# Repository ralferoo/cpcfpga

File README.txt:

PLEASE NOTE THAT THIS IS ONLY A PARTIAL REPOSITORY DUMP WHILE I TRY TO
SEPARATE PUBLIC AND PRIVATE PARTS...

-------------------------------------------------------------------------------

Contents
--------

This is the CPC FPGA project - a modern reimplementation of the Amstrad CPC
on an FPGA.

Whilst it's designed for use with the Amstrad CPC, the board could be
used for almost any 8-bit system. Alternatively, it could be used as a
cheap FPGA development board that includes a SCART socket, RAM, flash ROM,
PS/2 keyboard, twin joystick ports, tape input, etc...

The project is structured in these subdirectories:

bitstreams	Contains FPGA images that can be loaded from SD card
client		Contains Linux utilities to communicate with the board
datasheets	Miscellaneous datasheets (obtained publically, but are NOT
		part of this project)
docs		Various snippets of documentation I've written at various times
hardware/case	The case for revision 2 of CPC FPGA, for laser cutter use
hardware/eagle	The eagle schematic and circuit design for:
			homeboard30  (revision 1)
			homeboard99r (revision 2)
hardware/spice	Various spice analysis snippets
library/hdl	VHDL files that can be used in projects hosted on CPC FPGA
projects	Contains FPGA projects to be run on the CPC FPGA.
sidecar2	The firmware for the CPC FPGA suport chip
stuff		Old bits and bobs, to be deleted
Makefile	Used to build the system
README.txt	This file

-------------------------------------------------------------------------------

Building the CPC FPGA project
-----------------------------

The user part of CPC FPGA program can be built simply by running "make".

Other build targets:

all		Rebuild client and bitstreams
clean		Clean all build files, excluding final targets
bitstreams	Rebuild all the FPGA bitstream files

scan		Check to see if the CPC FPGA board is present
log		Keep an eye on the diagnostic log from the CPC FPGA board
dump		Dump the CPC FPGA image stored in the PROM
reload		Reload the CPC FPGA image stored in the PROM
xxx.load	Reload the CPC FPGA image for project xxx
xxx.program	Programs the CPC FPGA's PROM with the image for project xxx

sidecar2	Rebuild just the firmware
dfu		Install the firmware
reset		Resets the firmware

-------------------------------------------------------------------------------

LICENCES

The Atmega source code uses the LUFA library, licensed under the MIT library.
Please see licence/LUFA-License.txt for copyright information.

The schematic and board layout are currently licensed under the Creative
Commons Attribution-Share Alike 3.0.
Please see http://creativecommons.org/licenses/by-sa/3.0/ for more information.

If you make derivative works, you must license under a compatible licence
and include the following text:
Portions of this project are derived from CPC FPGA, (c) 2011-2013 Ranulf Doswell

Other than including the above attribution, you should rename the derivative
work so that it cannot be confused with the original CPC FPGA project, nor
can you refer to CPC FPGA in a manner that suggests the derivative work is
endorsed by CPC FGPA or used by CPC FPGA.

Any VHDL code is currently not open sourced unless explicitly mentioned.
The scope of the project is solely the hardware design and software for the
support chip.

If you need a commercial licence for the hardware portion of this project,
please contact licensing@ranulf.net for more information.

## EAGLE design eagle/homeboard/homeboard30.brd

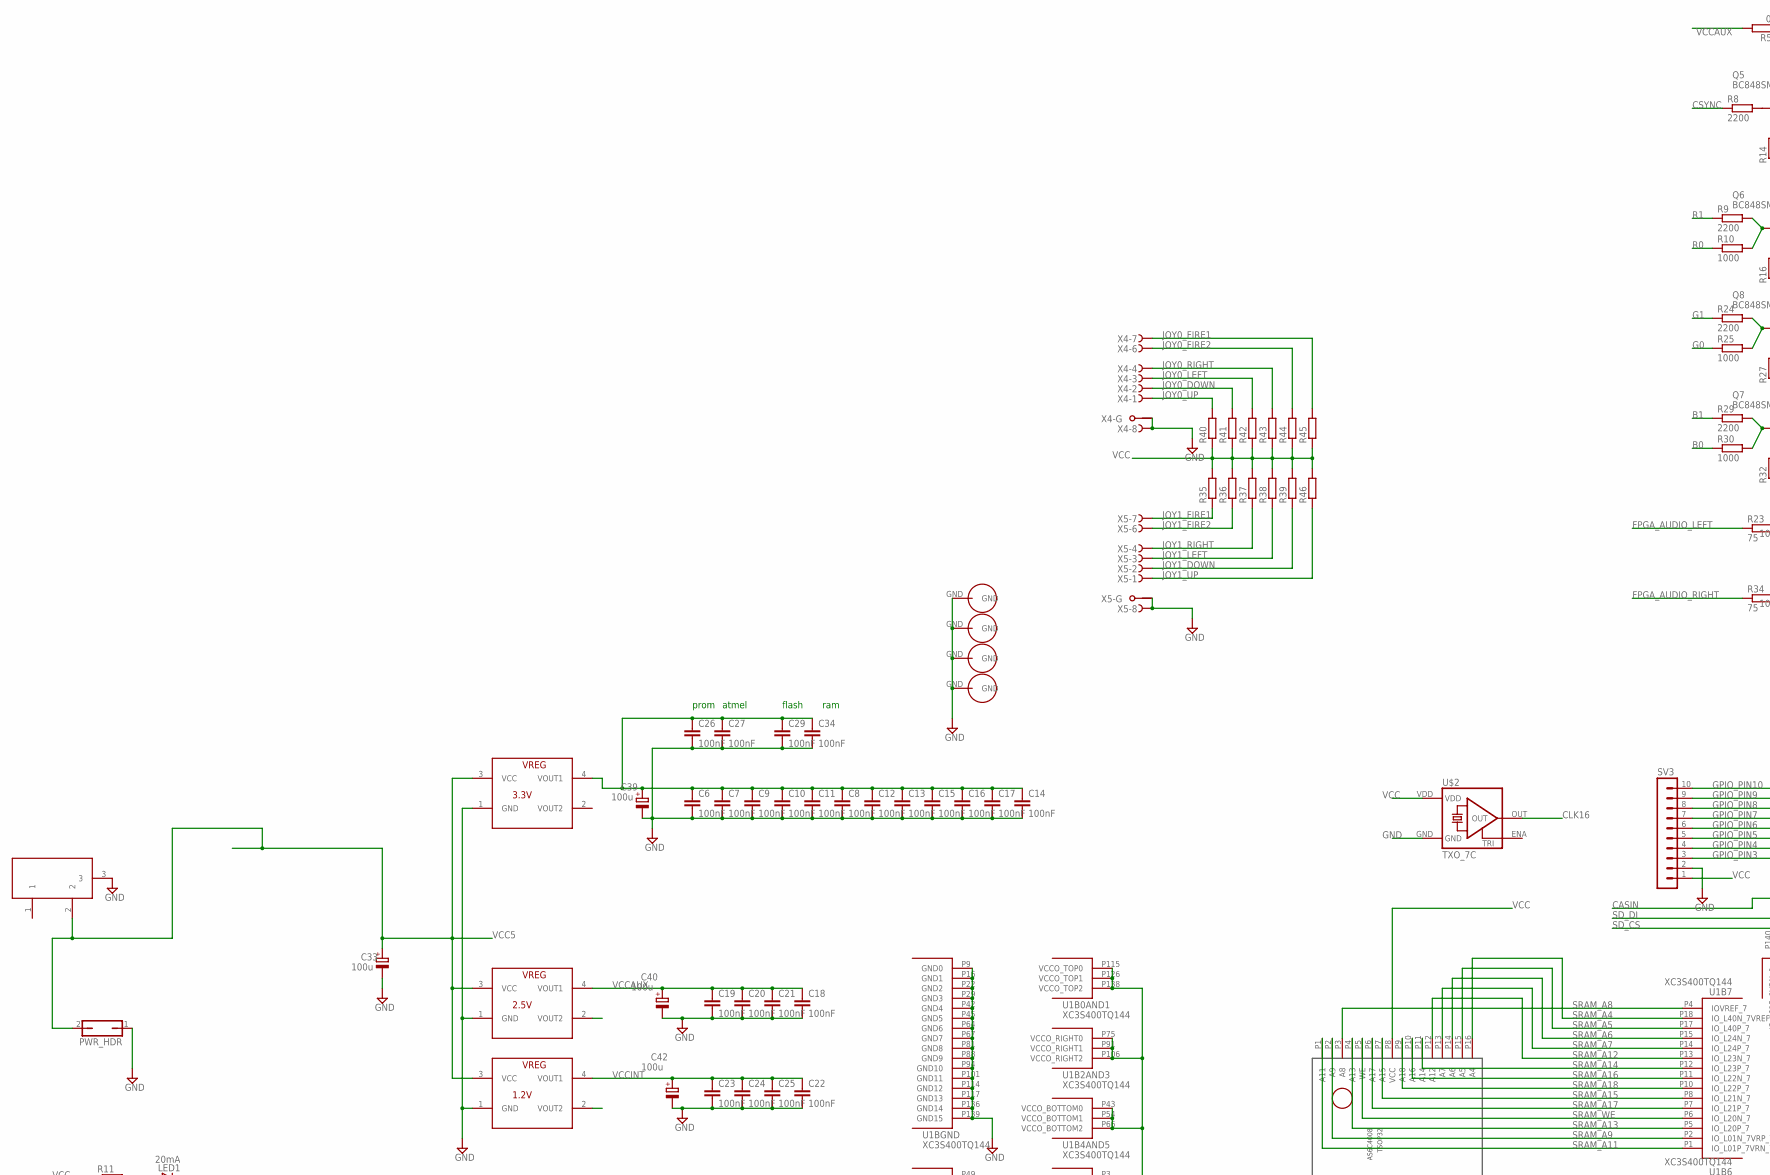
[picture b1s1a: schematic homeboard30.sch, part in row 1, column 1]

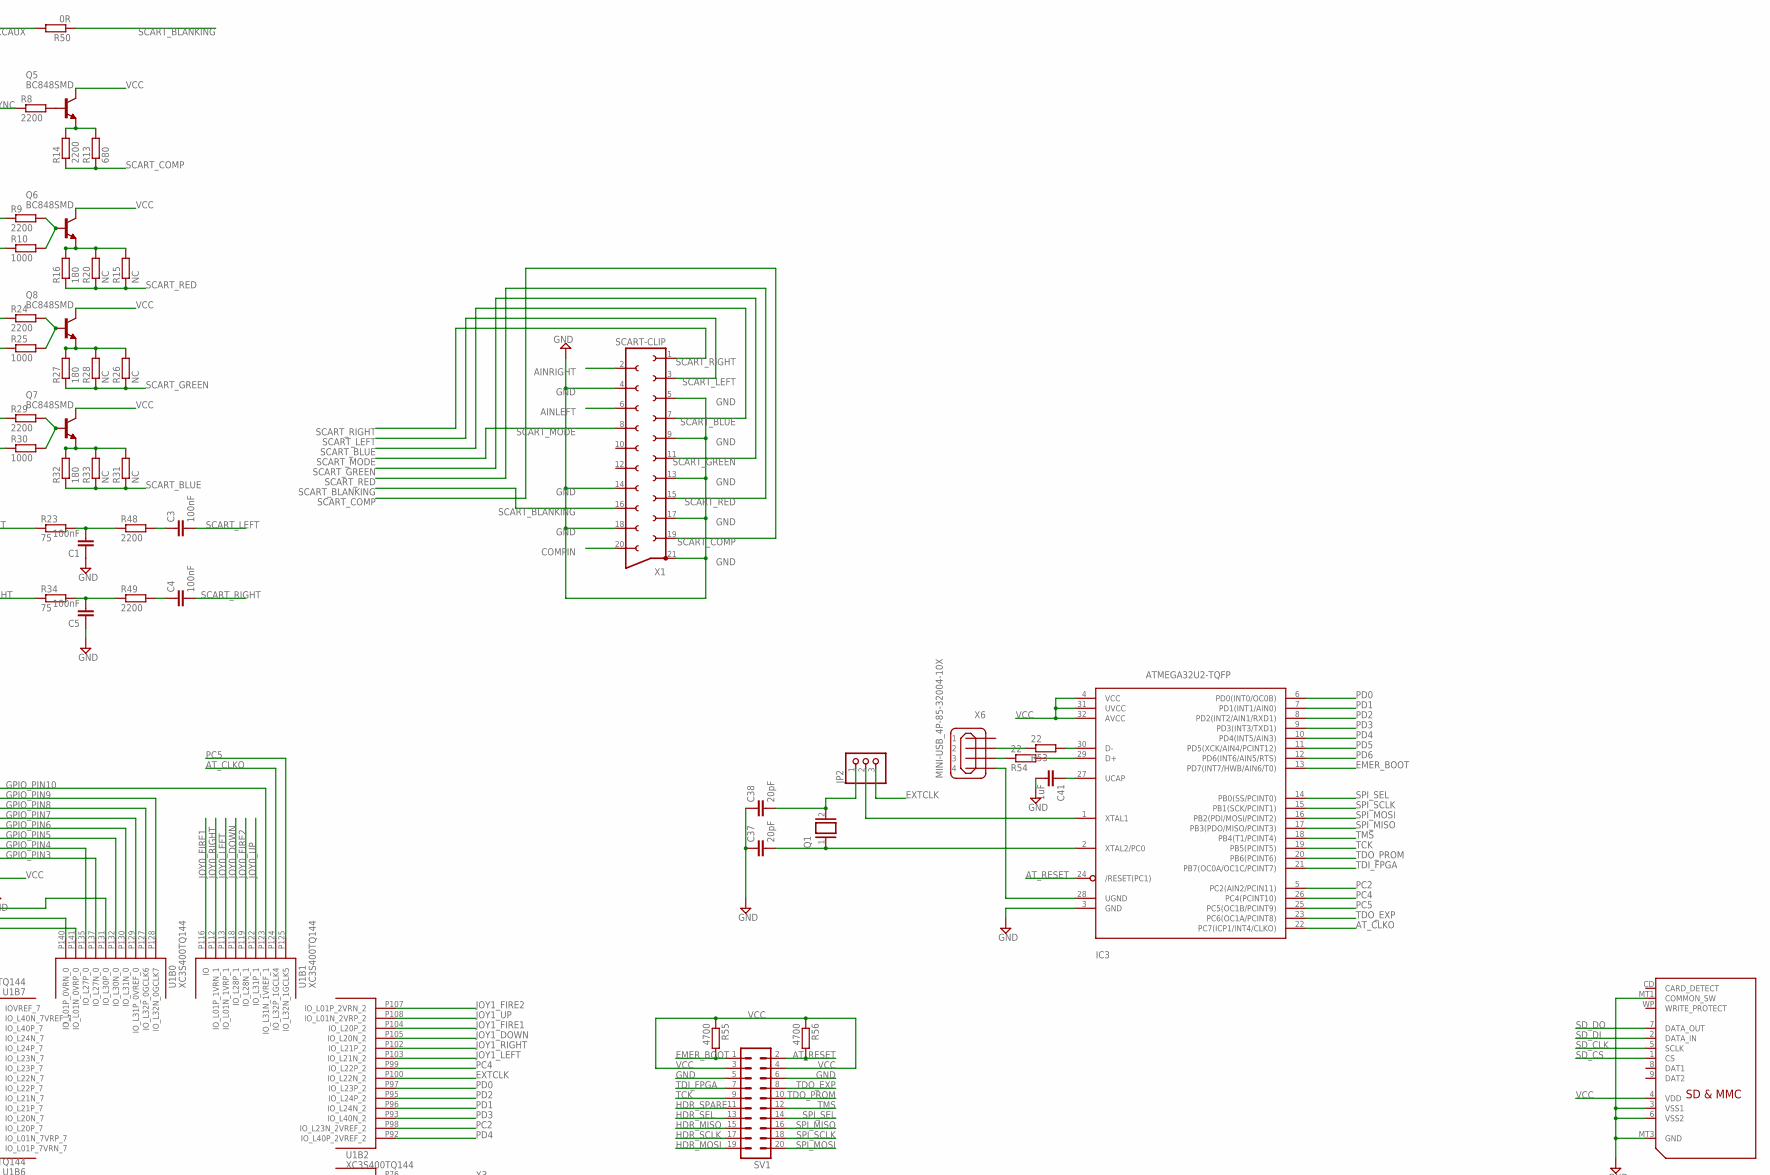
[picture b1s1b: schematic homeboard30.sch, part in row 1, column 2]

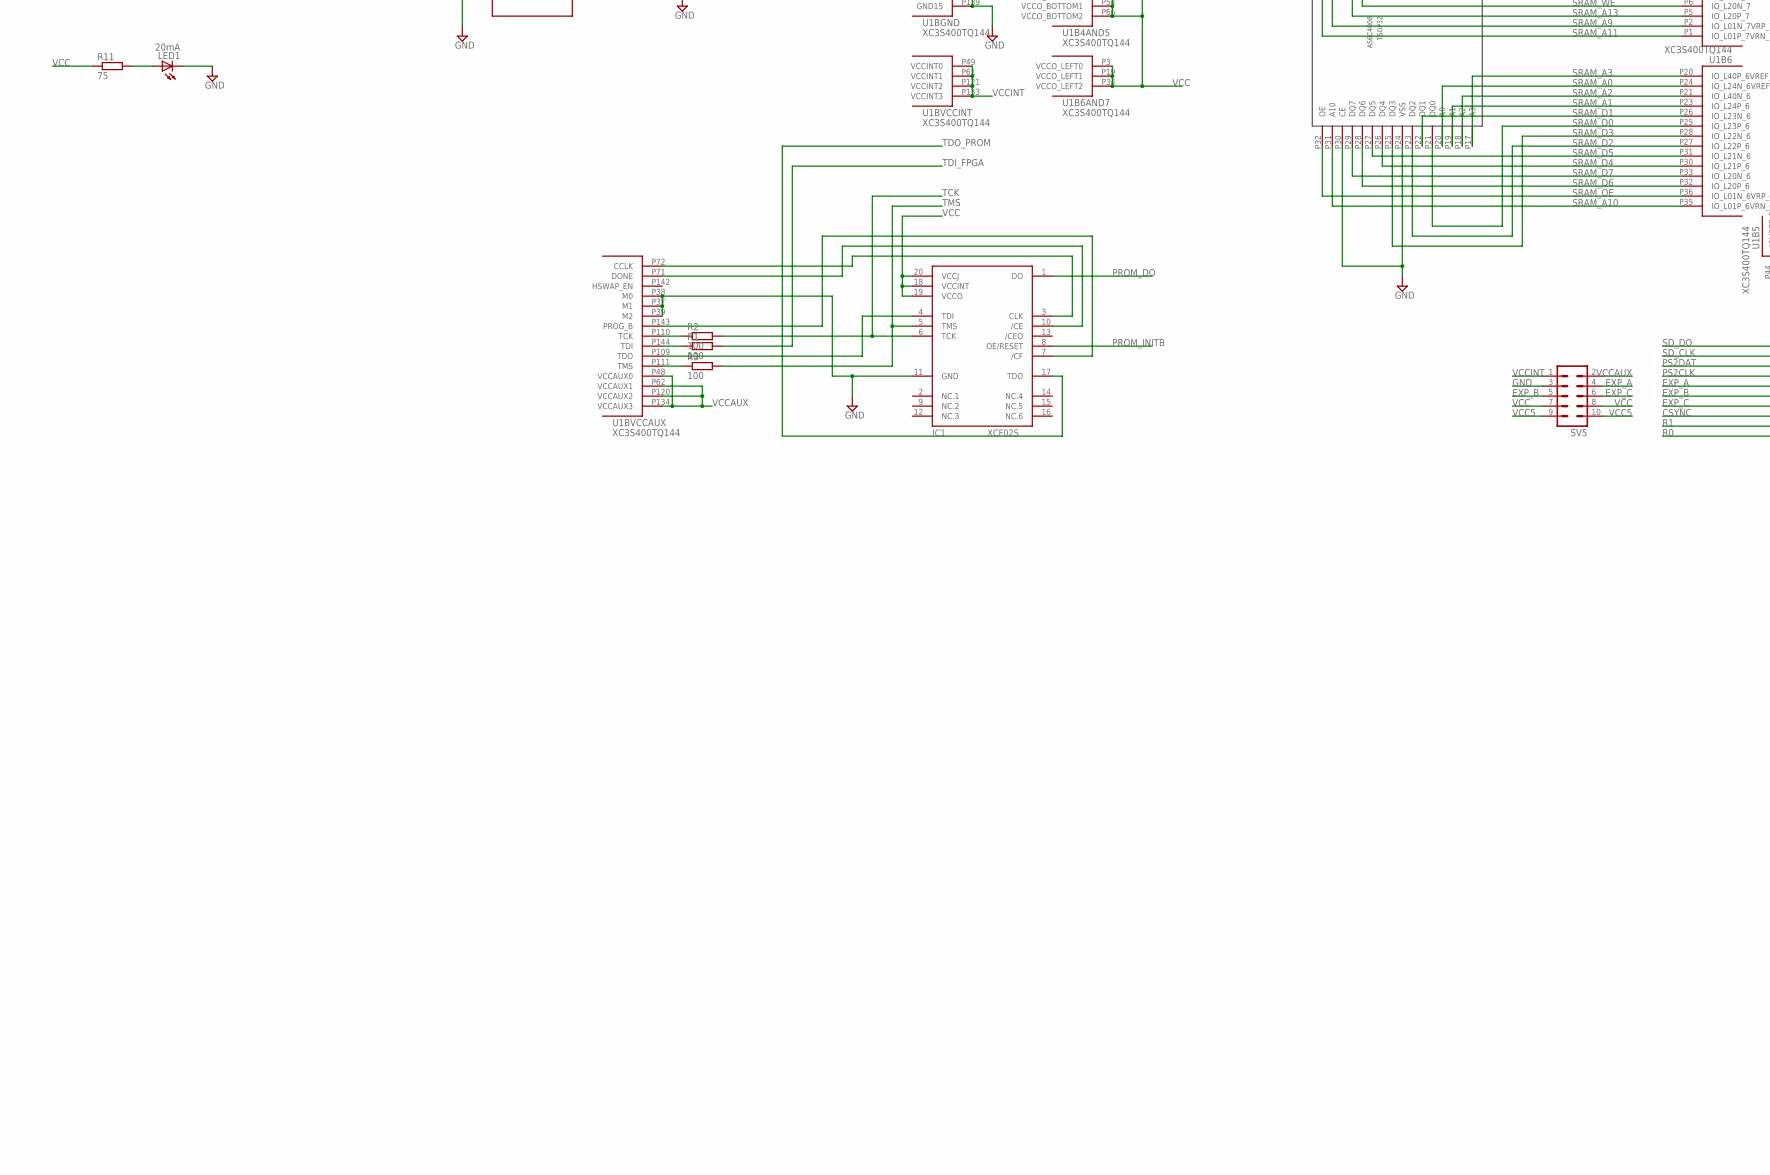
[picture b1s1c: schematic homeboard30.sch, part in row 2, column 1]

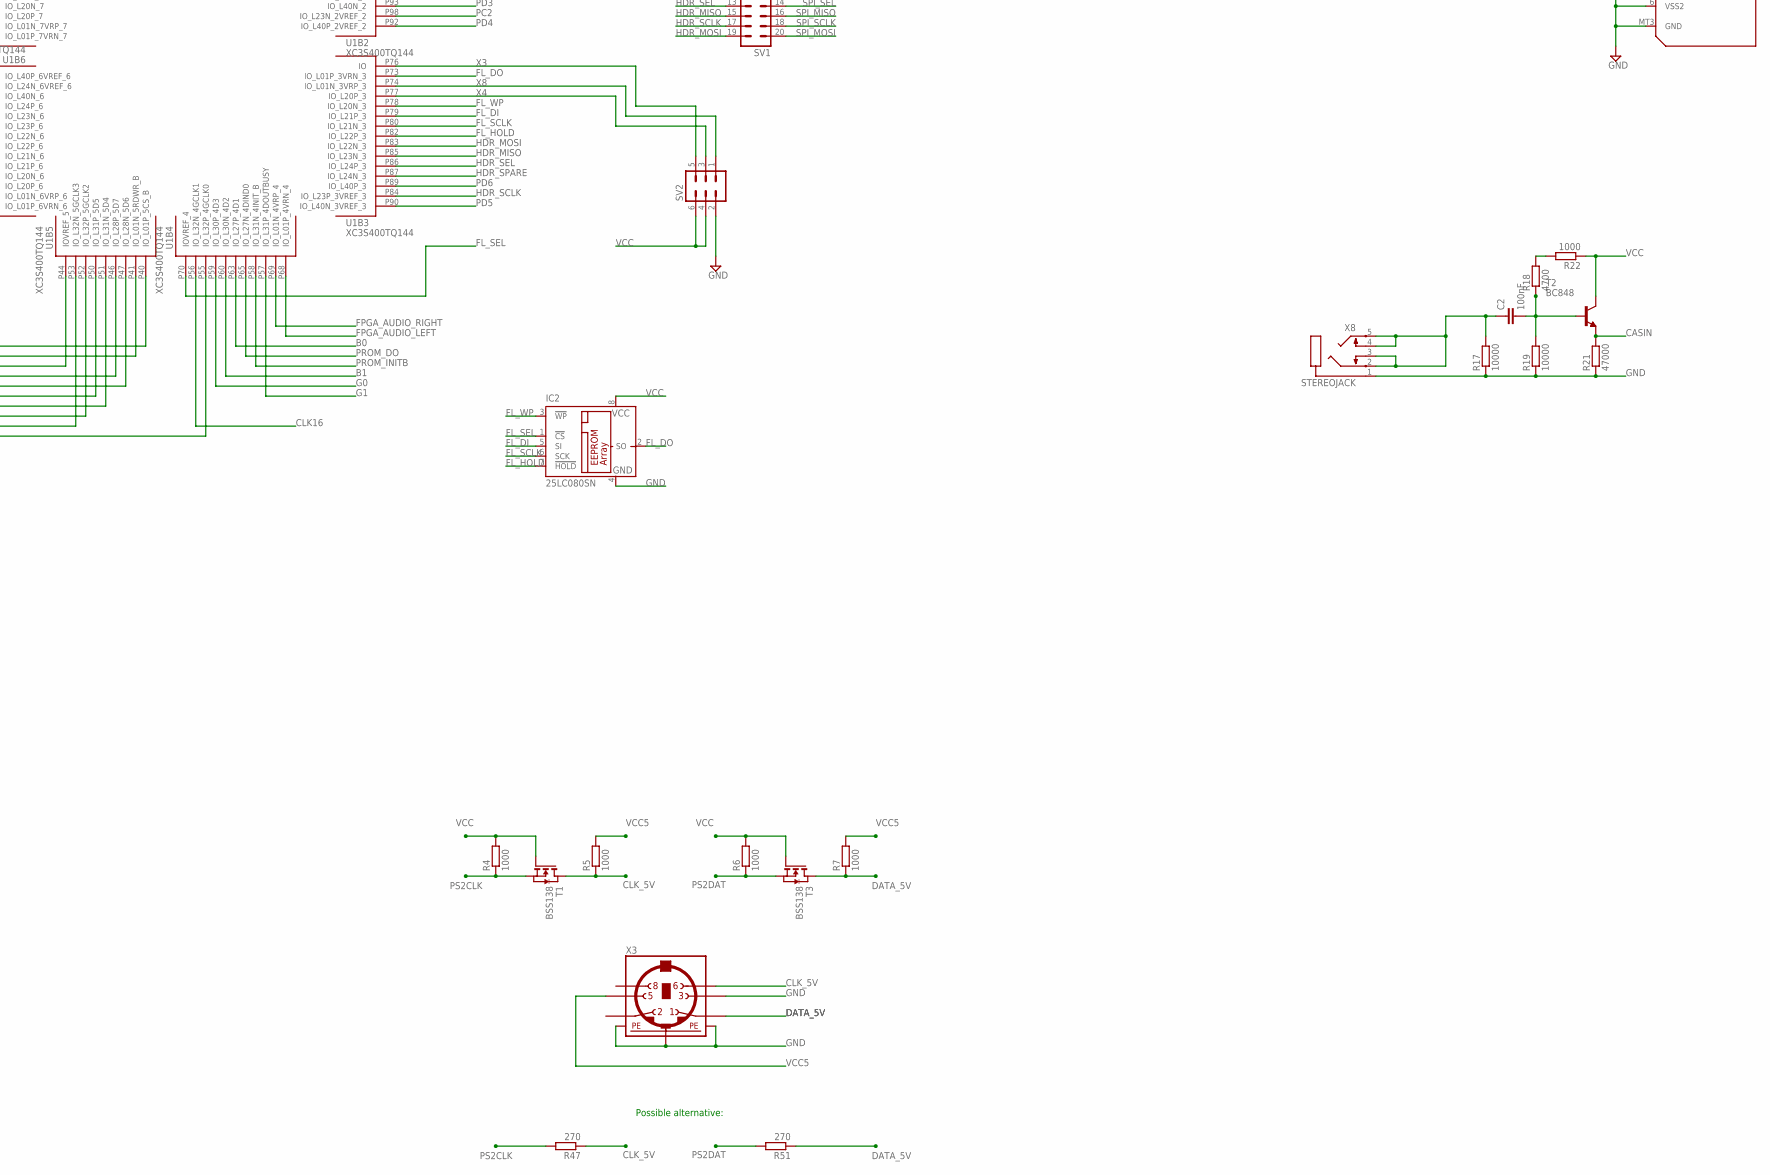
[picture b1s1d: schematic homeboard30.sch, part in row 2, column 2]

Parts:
C1, C2, C3, C4, C5, C6, C7, C8, C9, C10, C11, C12, C13, C14, C15, C16, C17, C18, C19, C20, C21, C22, C23, C24, C25, C26, C27, C29, C34: 100nF; C0603
C33, C39, C40, C42: 100u; PANASONIC_D
C37, C38: 20pF; C0805
C41: 1uF; C0805
IC1: XCF02S; VO20
IC2: 25LC080SN; SO-08
IC3: ATMEGA32U2-TQFP; TQFP32-08
JP2: PINHD-1X3; 1X03
LED1: 20mA; CHIPLED_0805
PWR_HDR: JP1Q; JP1
Q1: XTAL/S; QS
Q5, Q6, Q7, Q8: BC848SMD; SOT23
R1, R2, R3: 100; R0805
R4, R5, R6, R7, R10, R22, R25, R30: 1000; R0805
R8, R9, R14, R24, R29: 2200; R0805
R11, R23, R34: 75; M0805
R13: 680; R0805
R15, R20, R26, R28, R31, R33: NC; R0805
R16, R27, R32: 180; R0805
R17, R19: 10000; R0805
R18, R55, R56: 4700; R0805
R21: 47000; R0805
R35, R36, R37, R38, R39, R40, R41, R42, R43, R44, R45, R46: R-EU_M0805; M0805
R47, R51: 270; R0805
R48, R49: 2200; M0805
R50: 0R; M0805
R53, R54: 22; R0805
REG1.2: 1.2V; SOT223
REG2.5: 2.5V; SOT223
REG3.3: 3.3V; SOT223
SV1: MA10-2
SV2: MA03-2
SV3: MA10-1
SV5: MA05-2
T1, T3: BSS138; SOT-23
T2: BC848; SOT23
U1: XC3S400TQ144; TQ144
U$1, U$7, U$8, U$9: GNDHOLE
U$2: TXO_7C; OSC_7C
U$3: SDMMCNOHOLE; SDCARD-NOHOLE
U$6: AS6C4008; TSOP32
X1: SCART-CLIP
X3: MINI_DIN_6; M_DIN6
X4, X5: F09HPS; F09HP
X6: MINI-USB_4P-85-32004-10X; 85-32004-10X
X7: DC21MMX; DC-21MM
X8: STEREOJACK; 20-0137

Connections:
1: X7.1
AINLEFT: X1.6
AINRIGHT: X1.2
AT_CLKO: IC3.22 (PC7(ICP1/INT4/CLKO)), U1.P124 (IO_L32P_1GCLK4)
AT_RESET: IC3.24 (/RESET(PC1)), R56.2, SV1.2
B0: R30.1, U1.P63 (IO_L27P_4D1)
B1: R29.1, U1.P60 (IO_L30N_4D2)
CASIN: R21.2, T2.2 (E), U1.P131 (IO_L30P_0)
CLK16: U1.P56 (IO_L32N_4GCLK1), U$2.OUT
CLK_5V: R5.1, R47.1, T1.1 (D), X3.6
COMPIN: X1.20
CSYNC: R8.1, U1.P52 (IO_L32P_5GCLK2)
DATA_5V: R7.1, R51.1, T3.1 (D), X3.1
EMER_BOOT: IC3.13 (PD7(INT7/HWB/AIN6/T0)), R55.2, SV1.1
EXP_A: SV5.4, U1.P47 (IO_L28N_5D6)
EXP_B: SV5.5, U1.P50 (IO_L31P_5D5)
EXP_C: SV5.6, U1.P51 (IO_L31N_5D4)
EXTCLK: JP2.3, U1.P100 (IO_L22N_2)
FL_DI: IC2.5 (SI), U1.P79 (IO_L21P_3)
FL_DO: IC2.2 (SO), U1.P73 (IO_L01P_3VRN_3)
FL_HOLD: IC2.7 (!HOLD), U1.P82 (IO_L22P_3)
FL_SCLK: IC2.6 (SCK), U1.P80 (IO_L21N_3)
FL_SEL: IC2.1 (!CS), U1.P70 (IOVREF_4)
FL_WP: IC2.3 (!WP), U1.P78 (IO_L20N_3)
FPGA_AUDIO_LEFT: R23.1, U1.P68 (IO_L01P_4VRN_4)
FPGA_AUDIO_RIGHT: R34.1, U1.P69 (IO_L01N_4VRP_4)
G0: R25.1, U1.P59 (IO_L30P_4D3)
G1: R24.1, U1.P57 (IO_L31P_4DOUTBUSY)
GND: C1.1, C5.1, C6.2, C7.2, C8.2, C9.2, C10.2, C11.2, C12.2, C13.2, C14.2, C15.2, C16.2, C17.2, C18.2, C19.2, C20.2, C21.2, C22.2, C23.2, C24.2, C25.2, C26.2, C27.2, C29.2, C33.-, C34.2, C37.1, C38.1, C39.-, C40.-, C41.2, C42.-, IC1.11 (GND), IC2.4 (GND), IC3.3 (GND), LED1.C, PWR_HDR.1, R17.1, R19.1, R21.1, REG1.2.1 (GND), REG2.5.1 (GND), REG3.3.1 (GND), SV1.5, SV1.6, SV2.2, SV3.2, SV5.3, U1.P9 (GND0), U1.P16 (GND1), U1.P22 (GND2), U1.P29 (GND3), U1.P37 (M1), U1.P38 (M0), U1.P39 (M2), U1.P42 (GND4), U1.P45 (GND5), U1.P64 (GND6), U1.P67 (GND7), U1.P81 (GND8), U1.P88 (GND9), U1.P94 (GND10), U1.P101 (GND11), U1.P114 (GND12), U1.P117 (GND13), U1.P136 (GND14), U1.P139 (GND15), U$1.GND, U$2.GND, U$3.3 (VSS1), U$3.6 (VSS2), U$3.MT1 (COMMON_SW), U$3.MT3 (GND), U$6.P24 (VSS), U$6.P30 (CE), U$7.GND, U$8.GND, U$9.GND, X1.4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
GPIO_PIN3: SV3.3, U1.P137 (IO_L27N_0)
GPIO_PIN4: SV3.4, U1.P135 (IO_L27P_0)
GPIO_PIN5: SV3.5, U1.P132 (IO_L30N_0)
GPIO_PIN6: SV3.6, U1.P130 (IO_L31N_0)
GPIO_PIN7: SV3.7, U1.P129 (IO_L31P_0VREF_0)
GPIO_PIN8: SV3.8, U1.P127 (IO_L32P_0GCLK6)
GPIO_PIN9: SV3.9, U1.P128 (IO_L32N_0GCLK7)
GPIO_PIN10: SV3.10, U1.P123 (IO_L31N_1VREF_1)
HDR_MISO: SV1.15, U1.P85 (IO_L23N_3)
HDR_MOSI: SV1.19, U1.P83 (IO_L22N_3)
HDR_SCLK: SV1.17, U1.P84 (IO_L23P_3VREF_3)
HDR_SEL: SV1.13, U1.P86 (IO_L24P_3)
HDR_SPARE: SV1.11, U1.P87 (IO_L24N_3)
JOY0_DOWN: R41.2, U1.P118 (IO_L28P_1), X4.2 (F)
JOY0_FIRE1: R45.2, U1.P116 (IO), X4.7 (F)
JOY0_FIRE2: R44.2, U1.P119 (IO_L28N_1), X4.6 (F)
JOY0_LEFT: R42.2, U1.P113 (IO_L01N_1VRP_1), X4.3 (F)
JOY0_RIGHT: R43.2, U1.P112 (IO_L01P_1VRN_1), X4.4 (F)
JOY0_UP: R40.2, U1.P122 (IO_L31P_1), X4.1 (F)
JOY1_DOWN: R39.1, U1.P105 (IO_L20N_2), X5.2 (F)
JOY1_FIRE1: R35.1, U1.P104 (IO_L20P_2), X5.7 (F)
JOY1_FIRE2: R36.1, U1.P107 (IO_L01P_2VRN_2), X5.6 (F)
JOY1_LEFT: R38.1, U1.P103 (IO_L21N_2), X5.3 (F)
JOY1_RIGHT: R37.1, U1.P102 (IO_L21P_2), X5.4 (F)
JOY1_UP: R46.1, U1.P108 (IO_L01N_2VRP_2), X5.1 (F)
unnamed: IC3.1 (XTAL1), JP2.2
unnamed: C41.1, IC3.27 (UCAP)
unnamed: LED1.A, R11.2
unnamed: C37.2, IC3.2 (XTAL2/PC0), Q1.1
unnamed: C38.2, JP2.1, Q1.2
unnamed: IC1.3 (CLK), U1.P72 (CCLK)
unnamed: R53.1, X6.2
unnamed: IC1.10 (/CE), U1.P71 (DONE)
unnamed: R2.1, U1.P110 (TCK)
unnamed: IC1.7 (/CF), U1.P143 (PROG_B)
unnamed: R1.1, U1.P144 (TDI)
unnamed: R3.1, U1.P111 (TMS)
unnamed: IC3.29 (D+), R54.2
unnamed: C1.2, R23.2, R48.1
unnamed: C3.1, R48.2
unnamed: Q6.1 (B), R9.2, R10.2
unnamed: Q6.2 (E), R15.2, R16.2, R20.2
unnamed: Q8.1 (B), R24.2, R25.2
unnamed: Q8.2 (E), R26.2, R27.2, R28.2
unnamed: Q7.1 (B), R29.2, R30.2
unnamed: Q7.2 (E), R31.2, R32.2, R33.2
unnamed: Q5.2 (E), R13.2, R14.2
unnamed: C2.2, R18.1, R19.2, T2.1 (B)
unnamed: C2.1, R17.2, X8.2, X8.3, X8.4, X8.5
unnamed: R18.2, R22.2
unnamed: Q5.1 (B), R8.2
unnamed: C4.1, R49.2
unnamed: C5.2, R34.2, R49.1
unnamed: R54.1, X6.3
unnamed: IC3.30 (D-), R53.2
unnamed: IC3.28 (UGND), X6.4
PC2: IC3.5 (PC2(AIN2/PCIN11)), U1.P98 (IO_L23N_2VREF_2)
PC4: IC3.26 (PC4(PCINT10)), U1.P99 (IO_L22P_2)
PC5: IC3.25 (PC5(OC1B/PCINT9)), U1.P125 (IO_L32N_1GCLK5)
PD0: IC3.6 (PD0(INT0/OC0B)), U1.P97 (IO_L23P_2)
PD1: IC3.7 (PD1(INT1/AIN0)), U1.P96 (IO_L24N_2)
PD2: IC3.8 (PD2(INT2/AIN1/RXD1)), U1.P95 (IO_L24P_2)
PD3: IC3.9 (PD3(INT3/TXD1)), U1.P93 (IO_L40N_2)
PD4: IC3.10 (PD4(INT5/AIN3)), U1.P92 (IO_L40P_2VREF_2)
PD5: IC3.11 (PD5(XCK/AIN4/PCINT12)), U1.P90 (IO_L40N_3VREF_3)
PD6: IC3.12 (PD6(INT6/AIN5/RTS)), U1.P89 (IO_L40P_3)
PROM_DO: IC1.1 (DO), U1.P65 (IO_L27N_4DIND0)
PROM_INITB: IC1.8 (OE/RESET), U1.P58 (IO_L31N_4INIT_B)
PS2CLK: R4.1, R47.2, T1.2 (S), U1.P46 (IO_L28P_5D7)
PS2DAT: R6.1, R51.2, T3.2 (S), U1.P44 (IOVREF_5)
R0: R10.1, U1.P55 (IO_L32P_4GCLK0)
R1: R9.1, U1.P53 (IO_L32N_5GCLK3)
SCART_BLANKING: R50.1, X1.16
SCART_BLUE: R31.1, R32.1, R33.1, X1.7
SCART_COMP: R13.1, R14.1, X1.19
SCART_GREEN: R26.1, R27.1, R28.1, X1.11
SCART_LEFT: C3.2, X1.3
SCART_MODE: X1.8
SCART_RED: R15.1, R16.1, R20.1, X1.15
SCART_RIGHT: C4.2, X1.1
SD_CLK: U1.P41 (IO_L01N_5RDWR_B), U$3.5 (SCLK)
SD_CS: U1.P141 (IO_L01N_0VRP_0), U$3.1 (CS)
SD_DI: U1.P140 (IO_L01P_0VRN_0), U$3.2 (DATA_IN)
SD_DO: U1.P40 (IO_L01P_5CS_B), U$3.7 (DATA_OUT)
SPI_MISO: IC3.17 (PB3(PDO/MISO/PCINT3)), SV1.16
SPI_MOSI: IC3.16 (PB2(PDI/MOSI/PCINT2)), SV1.20
SPI_SCLK: IC3.15 (PB1(SCK/PCINT1)), SV1.18
SPI_SEL: IC3.14 (PB0(SS/PCINT0)), SV1.14
SRAM_A0: U1.P24 (IO_L24N_6VREF_6), U$6.P20 (A0)
SRAM_A1: U1.P23 (IO_L24P_6), U$6.P19 (A1)
SRAM_A2: U1.P21 (IO_L40N_6), U$6.P18 (A2)
SRAM_A3: U1.P20 (IO_L40P_6VREF_6), U$6.P17 (A3)
SRAM_A4: U1.P18 (IO_L40N_7VREF_7), U$6.P16 (A4)
SRAM_A5: U1.P17 (IO_L40P_7), U$6.P15 (A5)
SRAM_A6: U1.P15 (IO_L24N_7), U$6.P14 (A6)
SRAM_A7: U1.P14 (IO_L24P_7), U$6.P13 (A7)
SRAM_A8: U1.P4 (IOVREF_7), U$6.P3 (A8)
SRAM_A9: U1.P2 (IO_L01N_7VRP_7), U$6.P2 (A9)
SRAM_A10: U1.P35 (IO_L01P_6VRN_6), U$6.P31 (A10)
SRAM_A11: U1.P1 (IO_L01P_7VRN_7), U$6.P1 (A11)
SRAM_A12: U1.P13 (IO_L23N_7), U$6.P12 (A12)
SRAM_A13: U1.P5 (IO_L20P_7), U$6.P4 (A13)
SRAM_A14: U1.P12 (IO_L23P_7), U$6.P11 (A14)
SRAM_A15: U1.P8 (IO_L21N_7), U$6.P7 (A15)
SRAM_A16: U1.P11 (IO_L22N_7), U$6.P10 (A16)
SRAM_A17: U1.P7 (IO_L21P_7), U$6.P6 (A17)
SRAM_A18: U1.P10 (IO_L22P_7), U$6.P9 (A18)
SRAM_D0: U1.P25 (IO_L23P_6), U$6.P21 (DQ0)
SRAM_D1: U1.P26 (IO_L23N_6), U$6.P22 (DQ1)
SRAM_D2: U1.P27 (IO_L22P_6), U$6.P23 (DQ2)
SRAM_D3: U1.P28 (IO_L22N_6), U$6.P25 (DQ3)
SRAM_D4: U1.P30 (IO_L21P_6), U$6.P26 (DQ4)
SRAM_D5: U1.P31 (IO_L21N_6), U$6.P27 (DQ5)
SRAM_D6: U1.P32 (IO_L20P_6), U$6.P28 (DQ6)
SRAM_D7: U1.P33 (IO_L20N_6), U$6.P29 (DQ7)
SRAM_OE: U1.P36 (IO_L01N_6VRP_6), U$6.P32 (OE)
SRAM_WE: U1.P6 (IO_L20N_7), U$6.P5 (WE)
TCK: IC1.6 (TCK), IC3.19 (PB5(PCINT5)), R2.2, SV1.9
TDI_FPGA: IC3.21 (PB7(OC0A/OC1C/PCINT7)), R1.2, SV1.7
TDO_EXP: IC3.23 (PC6(OC1A/PCINT8)), SV1.8
TDO_FPGA: IC1.4 (TDI), U1.P109 (TDO)
TDO_PROM: IC1.17 (TDO), IC3.20 (PB6(PCINT6)), SV1.10
TMS: IC1.5 (TMS), IC3.18 (PB4(T1/PCINT4)), R3.2, SV1.12
VCC: C6.1, C7.1, C8.1, C9.1, C10.1, C11.1, C12.1, C13.1, C14.1, C15.1, C16.1, C17.1, C26.1, C27.1, C29.1, C34.1, C39.+, IC1.18 (VCCINT), IC1.19 (VCCO), IC1.20 (VCCJ), IC2.8 (VCC), IC3.4 (VCC), IC3.31 (UVCC), IC3.32 (AVCC), Q5.3 (C), Q6.3 (C), Q7.3 (C), Q8.3 (C), R4.2, R6.2, R11.1, R22.1, R35.2, R36.2, R37.2, R38.2, R39.2, R40.1, R41.1, R42.1, R43.1, R44.1, R45.1, R46.2, R55.1, R56.1, REG3.3.4 (VOUT1), SV1.3, SV1.4, SV2.4, SV2.6, SV3.1, SV5.7, SV5.8, T1.3 (G), T2.3 (C), T3.3 (G), U1.P3 (VCCO_LEFT0), U1.P19 (VCCO_LEFT1), U1.P34 (VCCO_LEFT2), U1.P43 (VCCO_BOTTOM0), U1.P54 (VCCO_BOTTOM1), U1.P66 (VCCO_BOTTOM2), U1.P75 (VCCO_RIGHT0), U1.P91 (VCCO_RIGHT1), U1.P106 (VCCO_RIGHT2), U1.P115 (VCCO_TOP0), U1.P126 (VCCO_TOP1), U1.P138 (VCCO_TOP2), U$2.VDD, U$3.4 (VDD), U$6.P8 (VCC)
VCC5: C33.+, PWR_HDR.2, R5.2, R7.2, REG1.2.3 (VCC), REG2.5.3 (VCC), REG3.3.3 (VCC), SV5.9, SV5.10, X3.5, X7.2
VCCAUX: C18.1, C19.1, C20.1, C21.1, C40.+, R50.2, REG2.5.4 (VOUT1), SV5.2, U1.P48 (VCCAUX0), U1.P62 (VCCAUX1), U1.P120 (VCCAUX2), U1.P134 (VCCAUX3)
VCCINT: C22.1, C23.1, C24.1, C25.1, C42.+, REG1.2.4 (VOUT1), SV5.1, U1.P49 (VCCINT0), U1.P61 (VCCINT1), U1.P121 (VCCINT2), U1.P133 (VCCINT3)
X3: SV2.5, U1.P76 (IO)
X4: SV2.3, U1.P77 (IO_L20P_3)
X8: SV2.1, U1.P74 (IO_L01N_3VRP_3)

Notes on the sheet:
Possible alternative:
atmel
prom
flash
ram

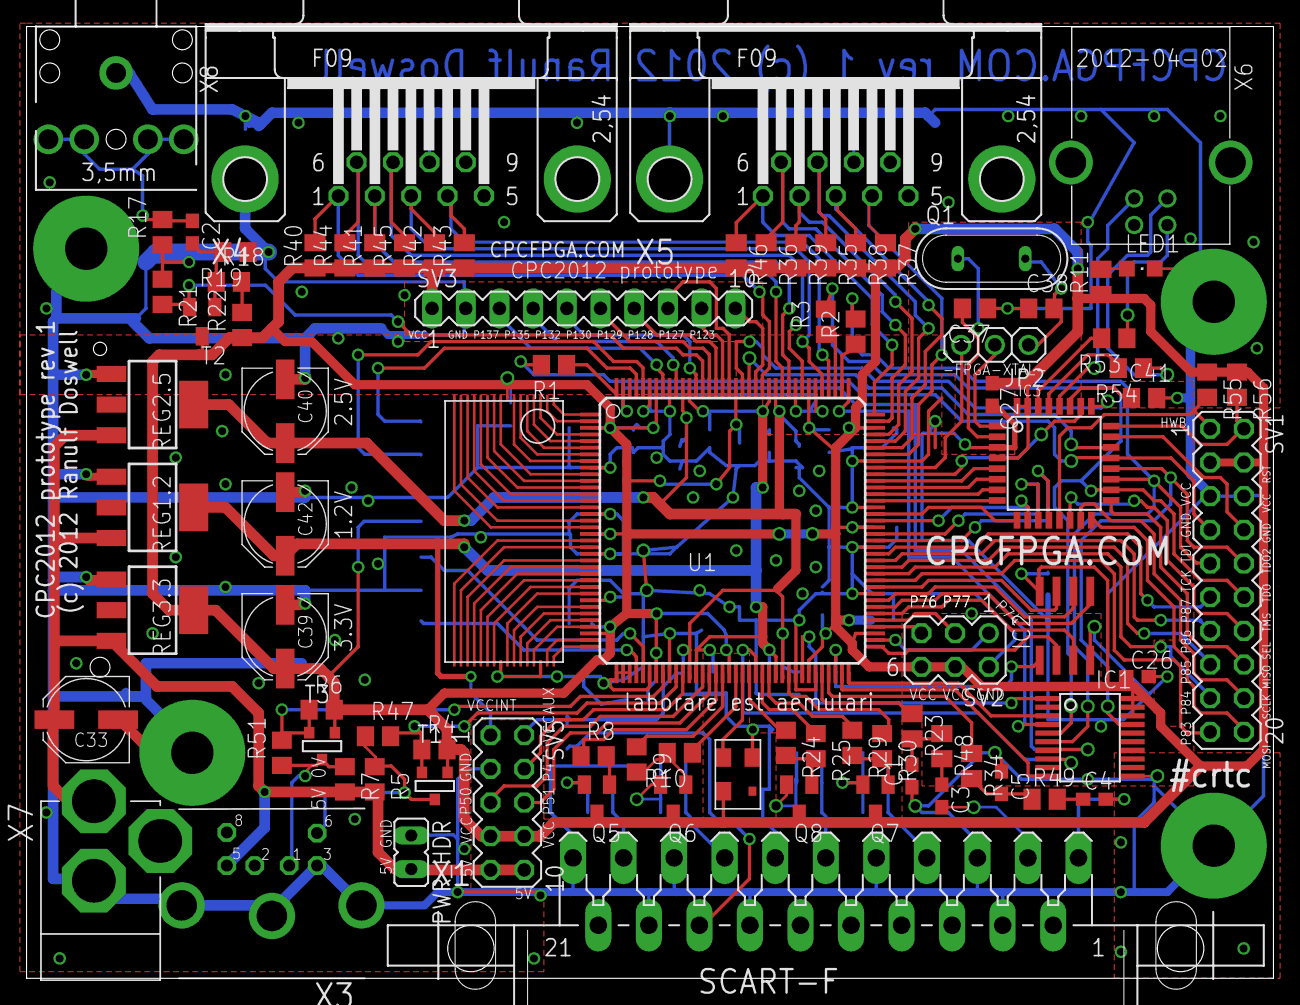
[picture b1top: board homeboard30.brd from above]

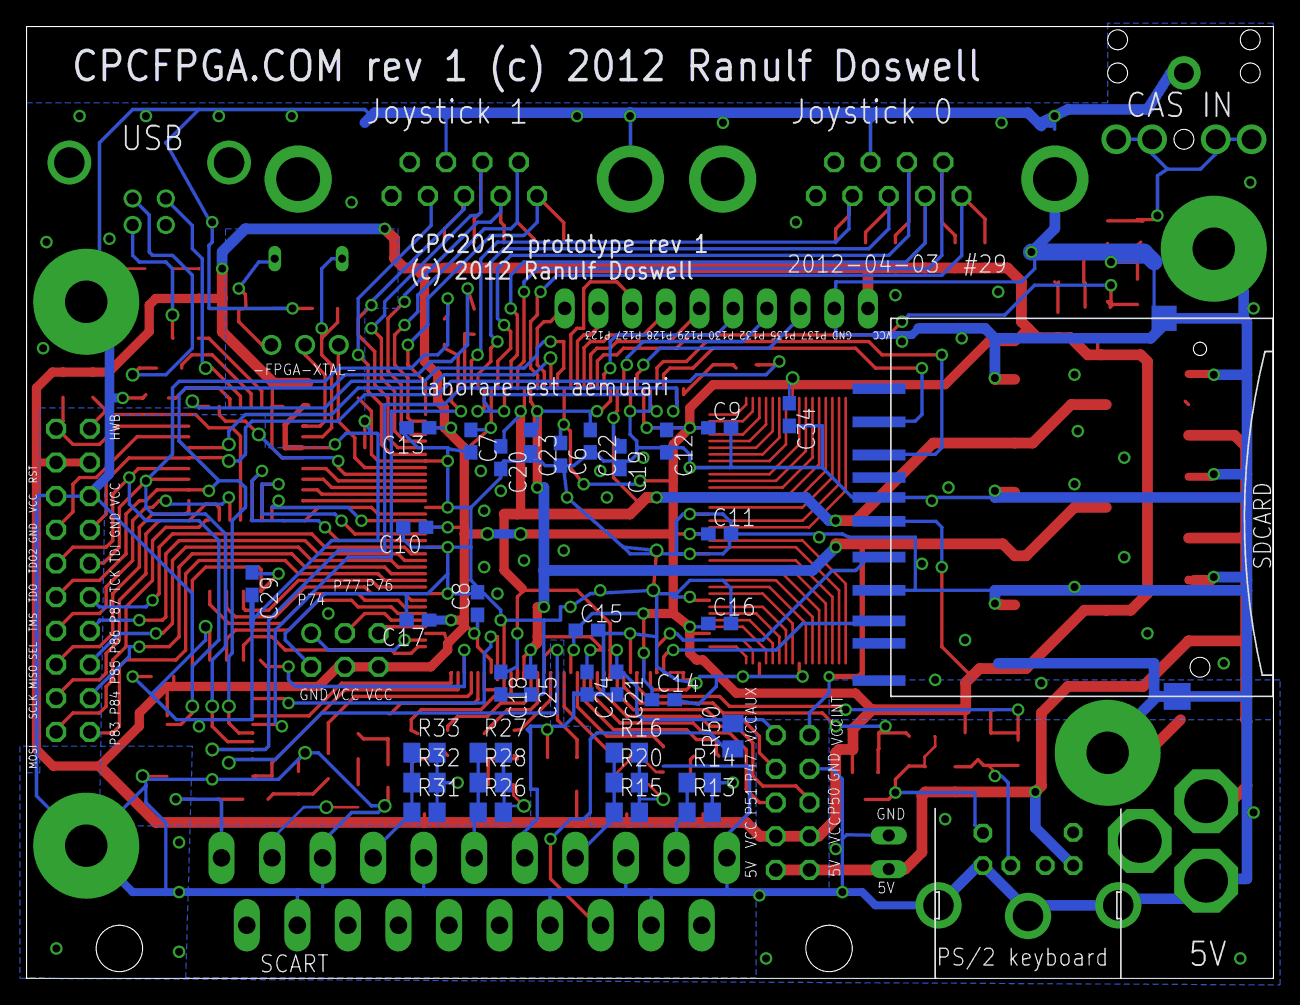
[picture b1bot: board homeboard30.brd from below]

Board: 2 copper layers, 94.0 x 71.8 mm, 126 parts (34 on the bottom side), 154 nets.

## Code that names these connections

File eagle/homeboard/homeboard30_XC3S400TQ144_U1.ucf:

# Generated by export-jtagtest-ucf.ulp
# http://www.jtagtest.com/
#
# Board      : C:/fpga/cpcfpga/eagle/homeboard/homeboard30.brd
# Part Name  : U1
# Part ID    : XC3S400TQ144
# Part pkg   : TQ144
# Exported on: 04.05.2012 17:41:37

NET "AT_CLKO" LOC = "P124";
NET "B0" LOC = "P63";
NET "B1" LOC = "P60";
NET "CASIN" LOC = "P131";
NET "CLK16" LOC = "P56";
NET "CSYNC" LOC = "P52";
NET "EXP_A" LOC = "P47";
NET "EXP_B" LOC = "P50";
NET "EXP_C" LOC = "P51";
NET "EXTCLK" LOC = "P100";
NET "FL_DI" LOC = "P79";
NET "FL_DO" LOC = "P73";
NET "FL_HOLD" LOC = "P82";
NET "FL_SCLK" LOC = "P80";
NET "FL_SEL" LOC = "P70";
NET "FL_WP" LOC = "P78";
NET "FPGA_AUDIO_LEFT" LOC = "P68";
NET "FPGA_AUDIO_RIGHT" LOC = "P69";
NET "G0" LOC = "P59";
NET "G1" LOC = "P57";
NET "GND" LOC = "P39";
NET "GND" LOC = "P37";
NET "GND" LOC = "P38";
NET "GND" LOC = "P139";
NET "GND" LOC = "P136";
NET "GND" LOC = "P117";
NET "GND" LOC = "P114";
NET "GND" LOC = "P101";
NET "GND" LOC = "P94";
NET "GND" LOC = "P88";
NET "GND" LOC = "P81";
NET "GND" LOC = "P67";
NET "GND" LOC = "P64";
NET "GND" LOC = "P45";
NET "GND" LOC = "P42";
NET "GND" LOC = "P29";
NET "GND" LOC = "P22";
NET "GND" LOC = "P16";
NET "GND" LOC = "P9";
NET "GPIO_PIN3" LOC = "P137";
NET "GPIO_PIN4" LOC = "P135";
NET "GPIO_PIN5" LOC = "P132";
NET "GPIO_PIN6" LOC = "P130";
NET "GPIO_PIN7" LOC = "P129";
NET "GPIO_PIN8" LOC = "P127";
NET "GPIO_PIN9" LOC = "P128";
NET "GPIO_PIN10" LOC = "P123";
NET "HDR_MISO" LOC = "P85";
NET "HDR_MOSI" LOC = "P83";
NET "HDR_SCLK" LOC = "P84";
NET "HDR_SEL" LOC = "P86";
NET "HDR_SPARE" LOC = "P87";
NET "JOY0_DOWN" LOC = "P118";
NET "JOY0_FIRE1" LOC = "P116";
NET "JOY0_FIRE2" LOC = "P119";
NET "JOY0_LEFT" LOC = "P113";
NET "JOY0_RIGHT" LOC = "P112";
NET "JOY0_UP" LOC = "P122";
NET "JOY1_DOWN" LOC = "P105";
NET "JOY1_FIRE1" LOC = "P104";
NET "JOY1_FIRE2" LOC = "P107";
NET "JOY1_LEFT" LOC = "P103";
NET "JOY1_RIGHT" LOC = "P102";
NET "JOY1_UP" LOC = "P108";
NET "N$35" LOC = "P72";
NET "N$38" LOC = "P71";
NET "N$39" LOC = "P110";
NET "N$40" LOC = "P143";
NET "N$42" LOC = "P144";
NET "N$43" LOC = "P111";
NET "PC2" LOC = "P98";
NET "PC4" LOC = "P99";
NET "PC5" LOC = "P125";
NET "PD0" LOC = "P97";
NET "PD1" LOC = "P96";
NET "PD2" LOC = "P95";
NET "PD3" LOC = "P93";
NET "PD4" LOC = "P92";
NET "PD5" LOC = "P90";
NET "PD6" LOC = "P89";
NET "PROM_DO" LOC = "P65";
NET "PROM_INITB" LOC = "P58";
NET "PS2CLK" LOC = "P46";
NET "PS2DAT" LOC = "P44";
NET "R0" LOC = "P55";
NET "R1" LOC = "P53";
NET "SD_CLK" LOC = "P41";
NET "SD_CS" LOC = "P141";
NET "SD_DI" LOC = "P140";
NET "SD_DO" LOC = "P40";
NET "SRAM_A0" LOC = "P24";
NET "SRAM_A1" LOC = "P23";
NET "SRAM_A2" LOC = "P21";
NET "SRAM_A3" LOC = "P20";
NET "SRAM_A4" LOC = "P18";
NET "SRAM_A5" LOC = "P17";
NET "SRAM_A6" LOC = "P15";
NET "SRAM_A7" LOC = "P14";
NET "SRAM_A8" LOC = "P4";
NET "SRAM_A9" LOC = "P2";
NET "SRAM_A10" LOC = "P35";
NET "SRAM_A11" LOC = "P1";
NET "SRAM_A12" LOC = "P13";
NET "SRAM_A13" LOC = "P5";
NET "SRAM_A14" LOC = "P12";
NET "SRAM_A15" LOC = "P8";
NET "SRAM_A16" LOC = "P11";
NET "SRAM_A17" LOC = "P7";
NET "SRAM_A18" LOC = "P10";
NET "SRAM_D0" LOC = "P25";
NET "SRAM_D1" LOC = "P26";
NET "SRAM_D2" LOC = "P27";
NET "SRAM_D3" LOC = "P28";
NET "SRAM_D4" LOC = "P30";
NET "SRAM_D5" LOC = "P31";
NET "SRAM_D6" LOC = "P32";
NET "SRAM_D7" LOC = "P33";
NET "SRAM_OE" LOC = "P36";
NET "SRAM_WE" LOC = "P6";
NET "TDO_FPGA" LOC = "P109";
NET "VCC" LOC = "P34";
NET "VCC" LOC = "P19";
NET "VCC" LOC = "P3";
NET "VCC" LOC = "P66";
NET "VCC" LOC = "P54";
NET "VCC" LOC = "P43";
NET "VCC" LOC = "P106";
NET "VCC" LOC = "P91";
NET "VCC" LOC = "P75";
NET "VCC" LOC = "P115";
NET "VCC" LOC = "P126";
NET "VCC" LOC = "P138";
NET "VCCAUX" LOC = "P62";
NET "VCCAUX" LOC = "P120";
NET "VCCAUX" LOC = "P134";
NET "VCCAUX" LOC = "P48";
NET "VCCINT" LOC = "P133";
NET "VCCINT" LOC = "P121";
NET "VCCINT" LOC = "P61";
NET "VCCINT" LOC = "P49";
NET "X3" LOC = "P76";
NET "X4" LOC = "P77";
NET "X8" LOC = "P74";

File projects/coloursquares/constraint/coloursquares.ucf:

# SYSTEM
#

# this is temporary clock... broken the real one :(
#NET "CLK48"		LOC = "P53"	| IOSTANDARD = LVCMOS33;
NET "CLK_48"		LOC = "P128"	| IOSTANDARD = LVCMOS33;
NET "CLK_48" TNM_NET = "CLK_48";
TIMESPEC "TS_CLK48" = PERIOD "CLK_48" 20.833ns HIGH 50%;

###########################################################################

# Keyboard shift regs
#
NET "JOY_IN_DATA"	LOC = "P46"	| IOSTANDARD = LVCMOS33;
NET "JOY_KEY_LATCH"	LOC = "P40"	| IOSTANDARD = LVCMOS33;
NET "JOY_KEY_CLK"	LOC = "P44"	| IOSTANDARD = LVCMOS33;
NET "KEY_OUT_DATA"	LOC = "P41"	| IOSTANDARD = LVCMOS33;

###########################################################################

# SCART
#
NET "SCART_CSYNC"	LOC = "P112"	| IOSTANDARD = LVCMOS33;
NET "SCART_R[1]"	LOC = "P77"	| IOSTANDARD = LVCMOS33;
NET "SCART_R[0]"	LOC = "P73"	| IOSTANDARD = LVCMOS33;
NET "SCART_G[1]"	LOC = "P78"	| IOSTANDARD = LVCMOS33;
NET "SCART_G[0]"	LOC = "P74"	| IOSTANDARD = LVCMOS33;
NET "SCART_B[1]"	LOC = "P79"	| IOSTANDARD = LVCMOS33;
NET "SCART_B[0]"	LOC = "P76"	| IOSTANDARD = LVCMOS33;
NET "SCART_AUDIO_LEFT"	LOC = "P80"	| IOSTANDARD = LVCMOS33;
NET "SCART_AUDIO_RIGHT"	LOC = "P82"	| IOSTANDARD = LVCMOS33;

###########################################################################

# HDMI
#
#NET "HDMI_DATA[11]"	LOC = "P108"	| IOSTANDARD = LVCMOS33;
#NET "HDMI_DATA[10]"	LOC = "P107"	| IOSTANDARD = LVCMOS33;
#NET "HDMI_DATA[9]"	LOC = "P105"	| IOSTANDARD = LVCMOS33;
#NET "HDMI_DATA[8]"	LOC = "P104"	| IOSTANDARD = LVCMOS33;
#NET "HDMI_DATA[7]"	LOC = "P103"	| IOSTANDARD = LVCMOS33;
#NET "HDMI_DATA[6]"	LOC = "P102"	| IOSTANDARD = LVCMOS33;
#NET "HDMI_DATA[5]"	LOC = "P99"	| IOSTANDARD = LVCMOS33;
#NET "HDMI_DATA[4]"	LOC = "P98"	| IOSTANDARD = LVCMOS33;
#NET "HDMI_DATA[3]"	LOC = "P97"	| IOSTANDARD = LVCMOS33;
#NET "HDMI_DATA[2]"	LOC = "P96"	| IOSTANDARD = LVCMOS33;
#NET "HDMI_DATA[1]"	LOC = "P95"	| IOSTANDARD = LVCMOS33;
#NET "HDMI_DATA[0]"	LOC = "P93"	| IOSTANDARD = LVCMOS33;
#NET "HDMI_IDCK"		LOC = "P100"	| IOSTANDARD = LVCMOS33;

#NET "HDMI_TFP_SDA"	LOC = "P92"	| IOSTANDARD = LVCMOS33 | PULLUP;
#NET "HDMI_TFP_SCL"	LOC = "P90"	| IOSTANDARD = LVCMOS33 | PULLUP;

#NET "HDMI_DE"		LOC = "P89"	| IOSTANDARD = LVCMOS33;
#NET "HDMI_HSYNC"	LOC = "P87"	| IOSTANDARD = LVCMOS33;
#NET "HDMI_VSYNC"	LOC = "P86"	| IOSTANDARD = LVCMOS33;

#NET "HDMI_SDA"		LOC = "P84"	| IOSTANDARD = LVCMOS33 | PULLUP;
#NET "HDMI_SCL"		LOC = "P83"	| IOSTANDARD = LVCMOS33 | PULLUP;
#NET "HDMI_CEC"		LOC = "P85"	| IOSTANDARD = LVCMOS33 | PULLUP;

###########################################################################

# SRAM
#
NET "SRAM_ADDRESS[0]"	LOC = "P24"	| IOSTANDARD = LVCMOS33;
NET "SRAM_ADDRESS[1]"	LOC = "P23"	| IOSTANDARD = LVCMOS33;
NET "SRAM_ADDRESS[2]"	LOC = "P21"	| IOSTANDARD = LVCMOS33;
NET "SRAM_ADDRESS[3]"	LOC = "P20"	| IOSTANDARD = LVCMOS33;
NET "SRAM_ADDRESS[4]"	LOC = "P18"	| IOSTANDARD = LVCMOS33;
NET "SRAM_ADDRESS[5]"	LOC = "P17"	| IOSTANDARD = LVCMOS33;
NET "SRAM_ADDRESS[6]"	LOC = "P15"	| IOSTANDARD = LVCMOS33;
NET "SRAM_ADDRESS[7]"	LOC = "P14"	| IOSTANDARD = LVCMOS33;
NET "SRAM_ADDRESS[8]"	LOC = "P4"	| IOSTANDARD = LVCMOS33;
NET "SRAM_ADDRESS[9]"	LOC = "P2"	| IOSTANDARD = LVCMOS33;
NET "SRAM_ADDRESS[10]"	LOC = "P35"	| IOSTANDARD = LVCMOS33;
NET "SRAM_ADDRESS[11]"	LOC = "P1"	| IOSTANDARD = LVCMOS33;
NET "SRAM_ADDRESS[12]"	LOC = "P13"	| IOSTANDARD = LVCMOS33;
NET "SRAM_ADDRESS[13]"	LOC = "P5"	| IOSTANDARD = LVCMOS33;
NET "SRAM_ADDRESS[14]"	LOC = "P12"	| IOSTANDARD = LVCMOS33;
NET "SRAM_ADDRESS[15]"	LOC = "P8"	| IOSTANDARD = LVCMOS33;
NET "SRAM_ADDRESS[16]"	LOC = "P11"	| IOSTANDARD = LVCMOS33;
NET "SRAM_ADDRESS[17]"	LOC = "P7"	| IOSTANDARD = LVCMOS33;
NET "SRAM_ADDRESS[18]"	LOC = "P10"	| IOSTANDARD = LVCMOS33;
NET "SRAM_DATA[0]"	LOC = "P25"	| IOSTANDARD = LVCMOS33;
NET "SRAM_DATA[1]"	LOC = "P26"	| IOSTANDARD = LVCMOS33;
NET "SRAM_DATA[2]"	LOC = "P27"	| IOSTANDARD = LVCMOS33;
NET "SRAM_DATA[3]"	LOC = "P28"	| IOSTANDARD = LVCMOS33;
NET "SRAM_DATA[4]"	LOC = "P30"	| IOSTANDARD = LVCMOS33;
NET "SRAM_DATA[5]"	LOC = "P31"	| IOSTANDARD = LVCMOS33;
NET "SRAM_DATA[6]"	LOC = "P32"	| IOSTANDARD = LVCMOS33;
NET "SRAM_DATA[7]"	LOC = "P33"	| IOSTANDARD = LVCMOS33;
NET "SRAM_OE"		LOC = "P36"	| IOSTANDARD = LVCMOS33;
NET "SRAM_WE"		LOC = "P6"	| IOSTANDARD = LVCMOS33;

###########################################################################

# TAPE / KEYBOARD / JOYSTICK
#
#NET "CASIN"		LOC = "P131"	| IOSTANDARD = LVCMOS33;

#NET "PS2_CLOCK"		LOC = "P118"	| IOSTANDARD = LVCMOS33;
#NET "PS2_DATA"		LOC = "P113"	| IOSTANDARD = LVCMOS33;

###########################################################################

# FLASH
#
#NET "FL_DO"	LOC = "P63"	| IOSTANDARD = LVCMOS33 | SLEW = FAST;
#NET "FL_SEL"	LOC = "P68"	| IOSTANDARD = LVCMOS33 | SLEW = FAST;
#NET "FL_DI"	LOC = "P69"	| IOSTANDARD = LVCMOS33 | SLEW = FAST;
#NET "FL_SCLK"	LOC = "P70"	| IOSTANDARD = LVCMOS33 | SLEW = FAST;

###########################################################################

# EXPANSION
#

#NET "GPIO0"	LOC = "P60"	| IOSTANDARD = LVCMOS33;
#NET "GPIO1"	LOC = "P59"	| IOSTANDARD = LVCMOS33;
#NET "GPIO2"	LOC = "P57"	| IOSTANDARD = LVCMOS33;
#NET "GPIO3"	LOC = "P56"	| IOSTANDARD = LVCMOS33;
#NET "GPIO4"	LOC = "P55"	| IOSTANDARD = LVCMOS33;
#NET "GPIO5"	LOC = "P53"	| IOSTANDARD = LVCMOS33;
#NET "GPIO6"	LOC = "P52"	| IOSTANDARD = LVCMOS33;
#NET "GPIO7"	LOC = "P51"	| IOSTANDARD = LVCMOS33;
#NET "GPIO8"	LOC = "P50"	| IOSTANDARD = LVCMOS33;
#NET "GPIO9"	LOC = "P47"	| IOSTANDARD = LVCMOS33;

#NET "PC2"		LOC = "P98"	| IOSTANDARD = LVCMOS33;
#NET "PC4"		LOC = "P99"	| IOSTANDARD = LVCMOS33;
#NET "PC5"		LOC = "P125"	| IOSTANDARD = LVCMOS33;

#NET "AVR_SS"		LOC = "P132"	| IOSTANDARD = LVCMOS33 | PULLUP;
#NET "AVR_SCLK"		LOC = "P130"	| IOSTANDARD = LVCMOS33 | PULLUP;
#NET "AVR_MOSI"		LOC = "P129"	| IOSTANDARD = LVCMOS33 | PULLUP;
#NET "AVR_MISO"		LOC = "P127"	| IOSTANDARD = LVCMOS33 | PULLUP;
#NET "PB4"		LOC = "P125"	| IOSTANDARD = LVCMOS33;
#NET "PB5"		LOC = "P124"	| IOSTANDARD = LVCMOS33;
#NET "PB6"		LOC = "P123"	| IOSTANDARD = LVCMOS33;
#NET "PB7"		LOC = "P122"	| IOSTANDARD = LVCMOS33;

#NET "SD_CLK"		LOC = "P140"	| IOSTANDARD = LVCMOS33 | PULLUP;
#NET "SD_CS"		LOC = "P135"	| IOSTANDARD = LVCMOS33 | PULLUP;
#NET "SD_DI"		LOC = "P137"	| IOSTANDARD = LVCMOS33 | PULLUP;
#NET "SD_DO"		LOC = "P141"	| IOSTANDARD = LVCMOS33 | PULLUP;
##NET "SD_SPARE"		LOC = "P131"	| IOSTANDARD = LVCMOS33;

#NET "TXD"		LOC = "P116"	| IOSTANDARD = LVCMOS33;
#NET "RXD"		LOC = "P119"	| IOSTANDARD = LVCMOS33;

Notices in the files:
eagle/homeboard/homeboard30.brd:
CPCFPGA.COM rev 1 (c) 2012 Ranulf Doswell
